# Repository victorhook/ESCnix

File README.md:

# ESCnix

An open source ESC that runs [Bluejay](https://github.com/bird-sanctuary/bluejay).

The main motivator behind this project is the lack of open source hardware designs for ESCs that can run open source firmware like Bluejay.

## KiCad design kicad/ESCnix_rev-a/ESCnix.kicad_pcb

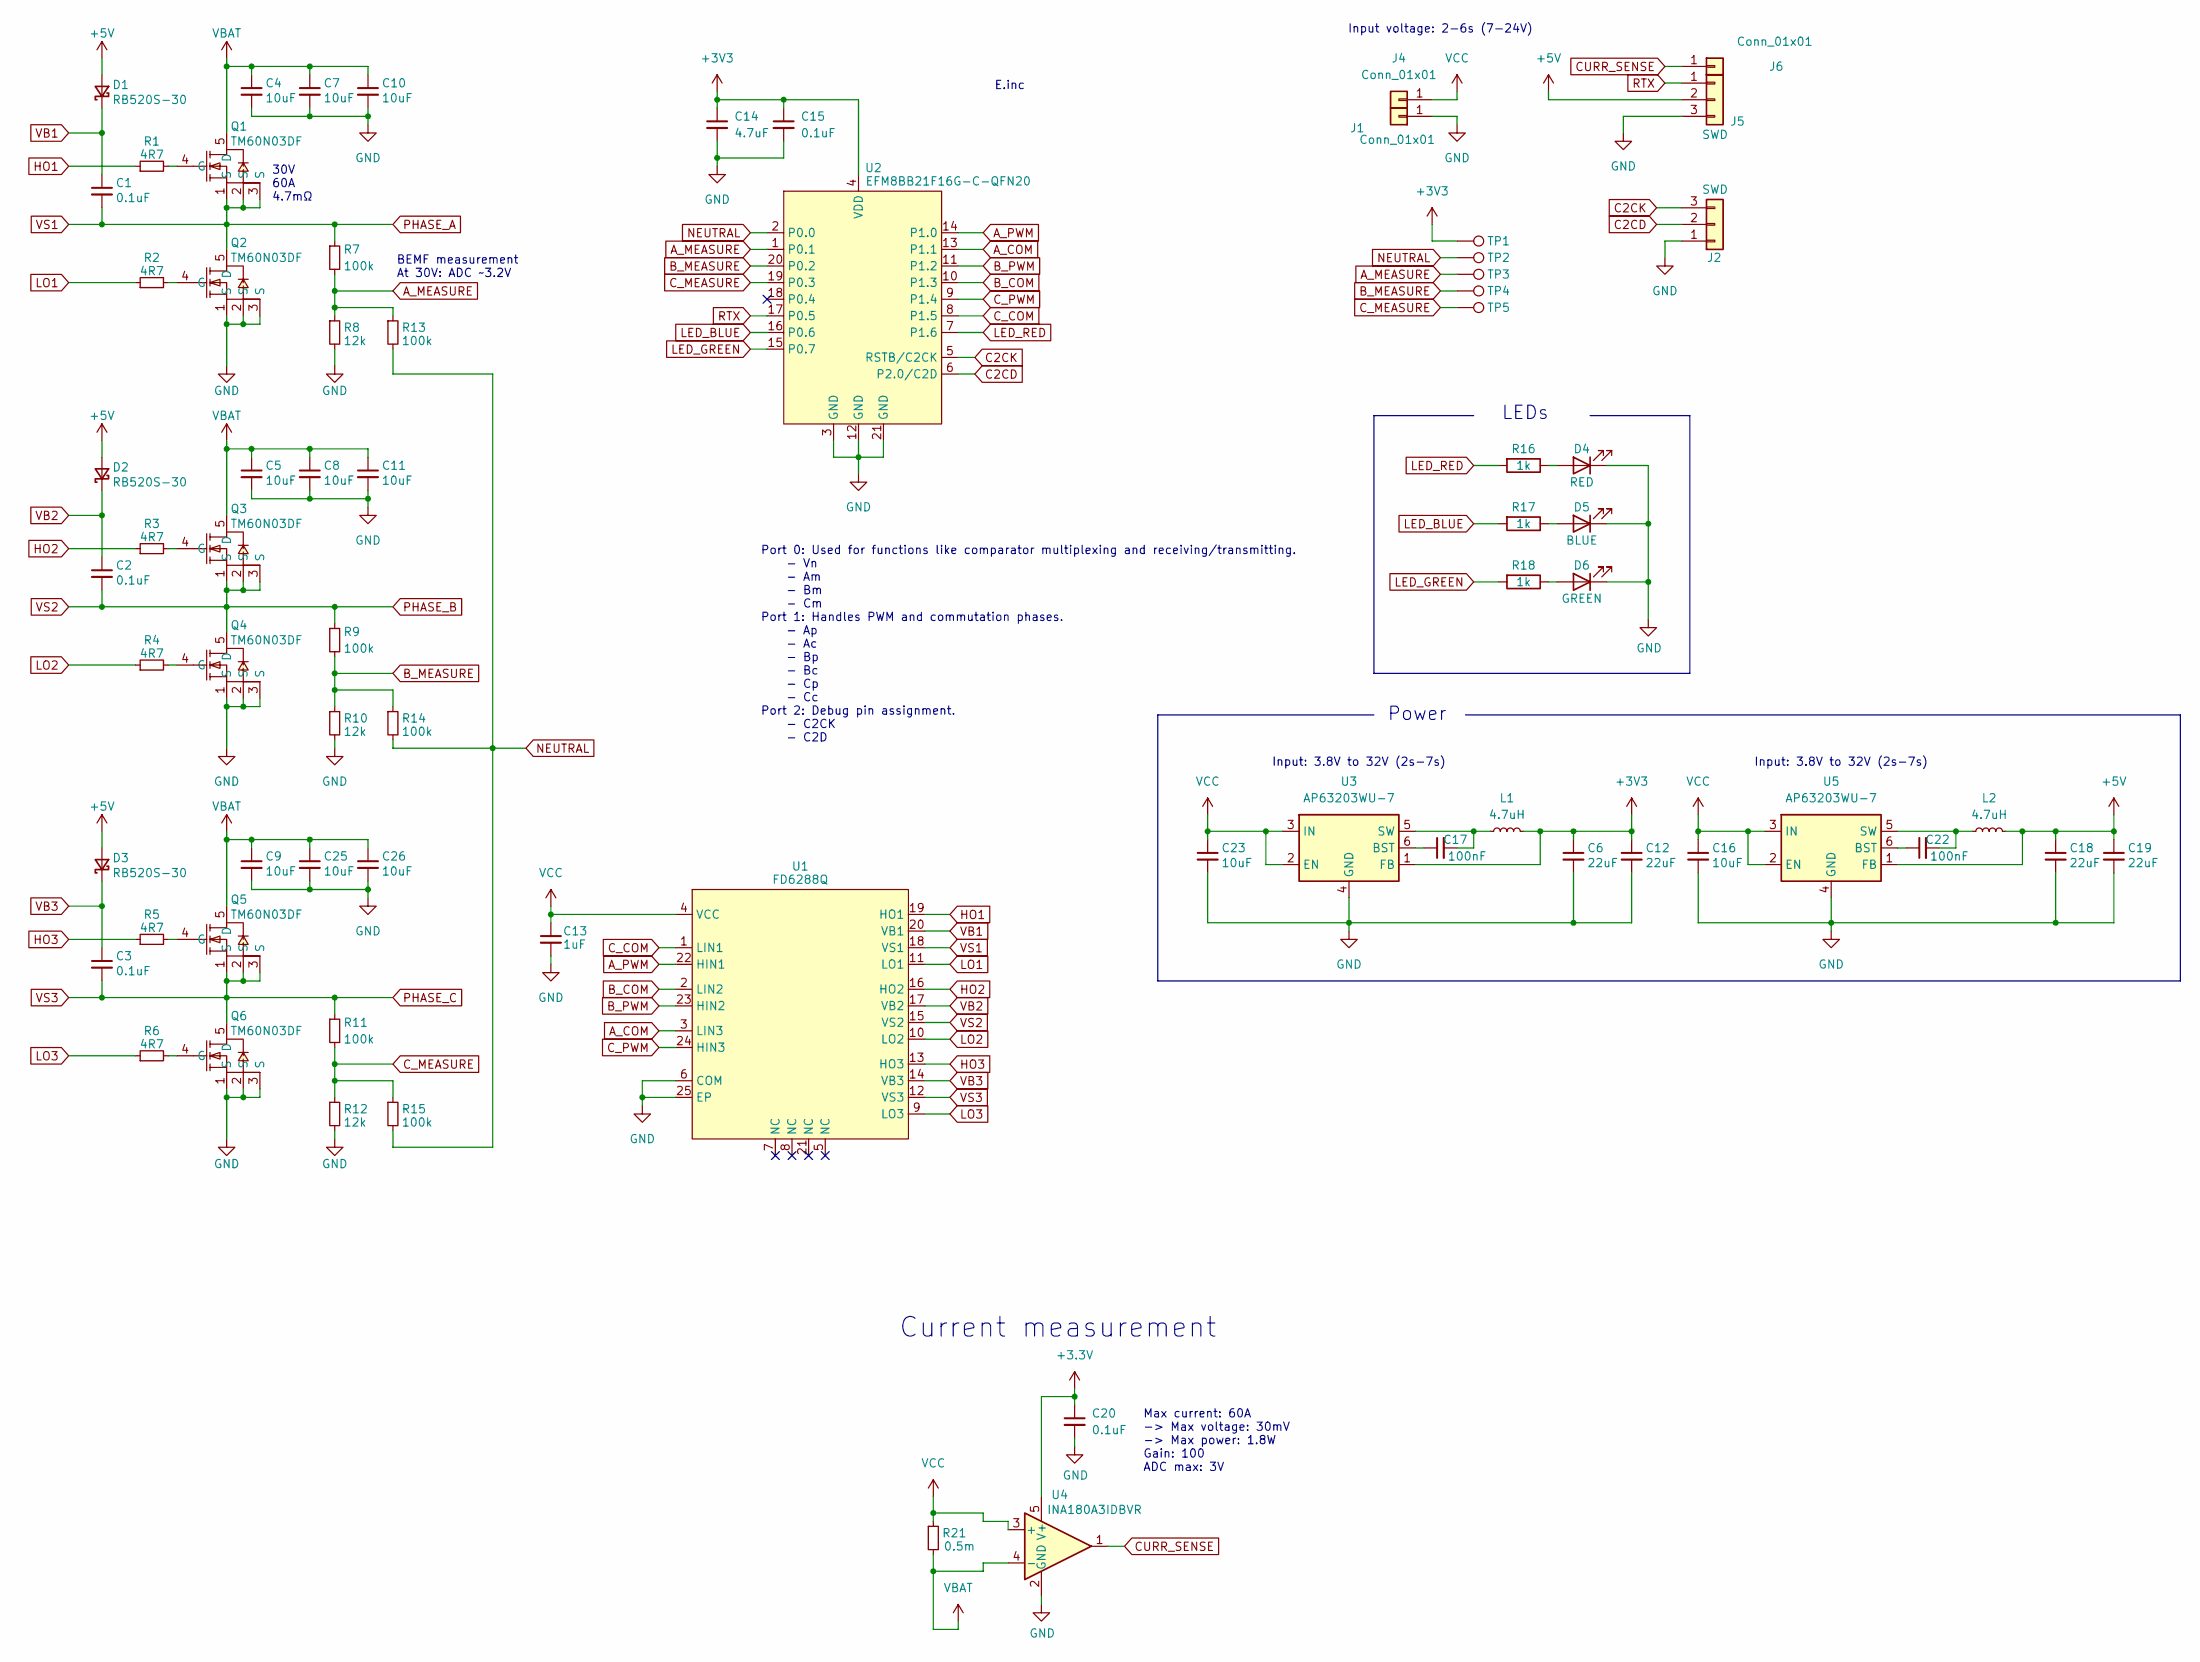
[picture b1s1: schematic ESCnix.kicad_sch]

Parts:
C1, C2, C3, C15, C20: 0.1uF; C_0402_1005Metric_NoSilk
C4, C5, C7, C8, C9, C10, C11, C16, C23, C25, C26: 10uF; C_0603_1608Metric_NoSilk; LCSC Part C96446
C6, C12, C18, C19: 22uF; C_0805_2012Metric_NoSilk; LCSC Part C45783
C13: 1uF; C_0402_1005Metric_NoSilk
C14: 4.7uF; C_0402_1005Metric_NoSilk
C17, C22: 100nF; C_0402_1005Metric_NoSilk
D1, D2, D3: RB520S-30; D_SOD-523_NoSilk
D4: RED; LED_0603_1608Metric_NoSilk
D5: BLUE; LED_0603_1608Metric_NoSilk
D6: GREEN; LED_0603_1608Metric_NoSilk
J1, J4: Conn_01x01; Conn_1_BigPad
J2: SWD; Conn_3_2_SMD
J5: SWD; Conn_3_Accesory2
J6: Conn_01x01; Conn_1_Accesory2
L1, L2: 4.7uH; L_0402_1005Metric
Q1, Q2, Q3, Q4, Q5, Q6: TM60N03DF; POWERDI3333-8_DMN7022LFGQ-7; LCSC Part C7422876
R1, R2, R3, R4, R5, R6: 4R7; R_0402_1005Metric_NoSilk; LCSC Part C162841
R7, R9, R11, R13, R14, R15: 100k; R_0402_1005Metric_NoSilk
R8, R10, R12: 12k; R_0402_1005Metric_NoSilk
R16, R17, R18: 1k; R_0402_1005Metric_NoSilk
R21: 0.5m; R_2512_6332Metric; LCSC Part C500733
TP1, TP2, TP3, TP4, TP5: TestPoint
U1: FD6288Q; QFN-24_L4.0-W4.0-P0.50-BL-EP2.6; LCSC Part C328453
U2: EFM8BB21F16G-C-QFN20; QFN-20_L3.0-W3.0-P0.50-BL-EP1.7_EFM8BB21F16G; LCSC Part C80713
U3: AP63203WU-7; TSOT-23-6; LCSC Part C780769
U4: INA180A3IDBVR; SOT-23-5; LCSC Part C122882
U5: AP63203WU-7; TSOT-23-6; LCSC Part C2071056

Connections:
+3.3V: C20.1, U4.5 (V+)
+3V3: C6.1, C12.1, C14.1, C15.1, L1.2, TP1.1, U2.4 (VDD), U3.1 (FB)
+5V: C18.1, C19.1, D1.2 (A), D2.2 (A), D3.2 (A), J5.2, L2.2, U5.1 (FB)
A_COM: U1.3 (LIN3), U2.13 (P1.1)
A_MEASURE: R7.2, R8.1, R13.1, TP3.1, U2.1 (P0.1)
A_PWM: U1.22 (HIN1), U2.14 (P1.0)
B_COM: U1.2 (LIN2), U2.10 (P1.3)
B_MEASURE: R9.2, R10.1, R14.1, TP4.1, U2.20 (P0.2)
B_PWM: U1.23 (HIN2), U2.11 (P1.2)
C2CD: J2.2, U2.6 (P2.0/C2D)
C2CK: J2.3, U2.5 (RSTB/C2CK)
CURR_SENSE: J6.1, U4.1
C_COM: U1.1 (LIN1), U2.8 (P1.5)
C_MEASURE: R11.2, R12.1, R15.1, TP5.1, U2.19 (P0.3)
C_PWM: U1.24 (HIN3), U2.9 (P1.4)
GND: C4.2, C5.2, C6.2, C7.2, C8.2, C9.2, C10.2, C11.2, C12.2, C13.2, C14.2, C15.2, C16.2, C18.2, C19.2, C20.2, C23.2, C25.2, C26.2, D4.1 (K), D5.1 (K), D6.1 (K), J1.1, J2.1, J5.3, Q2.1 (S), Q2.2 (S), Q2.3 (S), Q4.1 (S), Q4.2 (S), Q4.3 (S), Q6.1 (S), Q6.2 (S), Q6.3 (S), R8.2, R10.2, R12.2, U1.6 (COM), U1.25 (EP), U2.3 (GND), U2.12 (GND), U2.21 (GND), U3.4 (GND), U4.2 (GND), U5.4 (GND)
HO1: R1.1, U1.19 (HO1)
HO2: R3.1, U1.16 (HO2)
HO3: R5.1, U1.13 (HO3)
LED_BLUE: R17.2, U2.16 (P0.6)
LED_GREEN: R18.2, U2.15 (P0.7)
LED_RED: R16.2, U2.7 (P1.6)
LO1: R2.1, U1.11 (LO1)
LO2: R4.1, U1.10 (LO2)
LO3: R6.1, U1.9 (LO3)
NEUTRAL: R13.2, R14.2, R15.2, TP2.1, U2.2 (P0.0)
unnamed: D4.2 (A), R16.1
unnamed: D5.2 (A), R17.1
unnamed: D6.2 (A), R18.1
unnamed: Q1.4 (G), R1.2
unnamed: Q2.4 (G), R2.2
unnamed: Q3.4 (G), R3.2
unnamed: Q4.4 (G), R4.2
unnamed: Q5.4 (G), R5.2
unnamed: Q6.4 (G), R6.2
unnamed: C17.1, U3.6 (BST)
unnamed: C17.2, L1.1, U3.5 (SW)
unnamed: C22.1, U5.6 (BST)
unnamed: C22.2, L2.1, U5.5 (SW)
PHASE_A: C1.2, Q1.1 (S), Q1.2 (S), Q1.3 (S), Q2.5 (D), R7.1, U1.18 (VS1)
PHASE_B: C2.2, Q3.1 (S), Q3.2 (S), Q3.3 (S), Q4.5 (D), R9.1, U1.15 (VS2)
PHASE_C: C3.2, Q5.1 (S), Q5.2 (S), Q5.3 (S), Q6.5 (D), R11.1, U1.12 (VS3)
RTX: J5.1, U2.17 (P0.5)
VB1: C1.1, D1.1 (K), U1.20 (VB1)
VB2: C2.1, D2.1 (K), U1.17 (VB2)
VB3: C3.1, D3.1 (K), U1.14 (VB3)
VBAT: C4.1, C5.1, C7.1, C8.1, C9.1, C10.1, C11.1, C25.1, C26.1, Q1.5 (D), Q3.5 (D), Q5.5 (D), R21.2, U4.4 (-)
VCC: C13.1, C16.1, C23.1, J4.1, R21.1, U1.4 (VCC), U3.2 (EN), U3.3 (IN), U4.3 (+), U5.2 (EN), U5.3 (IN)

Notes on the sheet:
Input: 3.8V to 32V (2s-7s)
Port 0: Used for functions like comparator multiplexing and receiving/transmitting. - Vn - Am - Bm - Cm Port 1: Handles PWM and commutation phases. - Ap - Ac - Bp - Bc - Cp - Cc Port 2: Debug pin assignment. - C2CK - C2D
E.inc
BEMF measurement At 30V: ADC ~3.2V
30V 60A 4.7mΩ
Max current: 60A -> Max voltage: 30mV -> Max power: 1.8W Gain: 100 ADC max: 3V
LEDs
Power
Input voltage: 2-6s (7-24V)
Current measurement

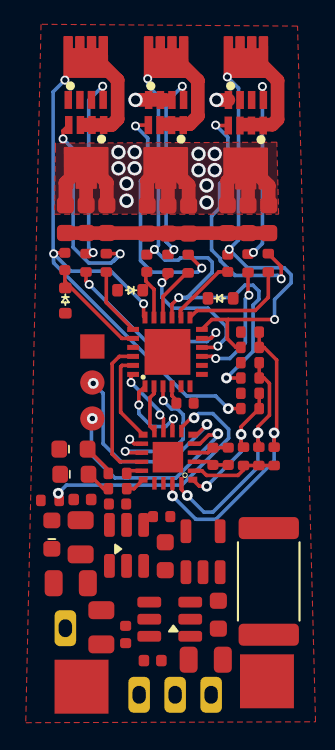
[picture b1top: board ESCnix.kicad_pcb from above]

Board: 4 copper layers, 67 parts (0 on the bottom side), 48 nets.

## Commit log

2024-10-08 Schematic close to complete! Started layout
2024-10-12 Initial layout done, started routing a bit
